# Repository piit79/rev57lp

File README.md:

# Rev57LP

(Formerly known by no-one as Reviung-ish56 LP :)

Low-profile 57-key ergonomic keyboard inspired by Reviung41. Uses hotswap sockets for Kailh Choc V1 (PG1350) switches.

Based on [reviung-ish](https://github.com/fredbabe/reviung_ish_pcb) by oddkeeb.

Main differences from Reviung41:

* Added number row
* Added two more bottom row keys
* Added one extra middle key
* Uses hotswap sockets for Kailh Choc V1 switches with Choc spacing (18x17 mm)

Further modifications made by 42. Keebs:

* 2x 1u space key instead of a 2u with a Choc stabiliser, because nobody likes stabs
* Slightly increased angle of the sides from 13° to 15°
* Added power switch and a battery footprint
* Mounting holes changed to through holes for 3 mm diameter brass standoffs
* Dropped the middle matrix column to free up one I/O pin
* Added stacked acrylic case consisting of switch, middle and bottom plates

Full kit available for purchase at [42. Keebs](https://42keebs.eu/shop/kits/pro-micro-based/rev57lp-50-low-profile-hotswap-ergo-kit/).

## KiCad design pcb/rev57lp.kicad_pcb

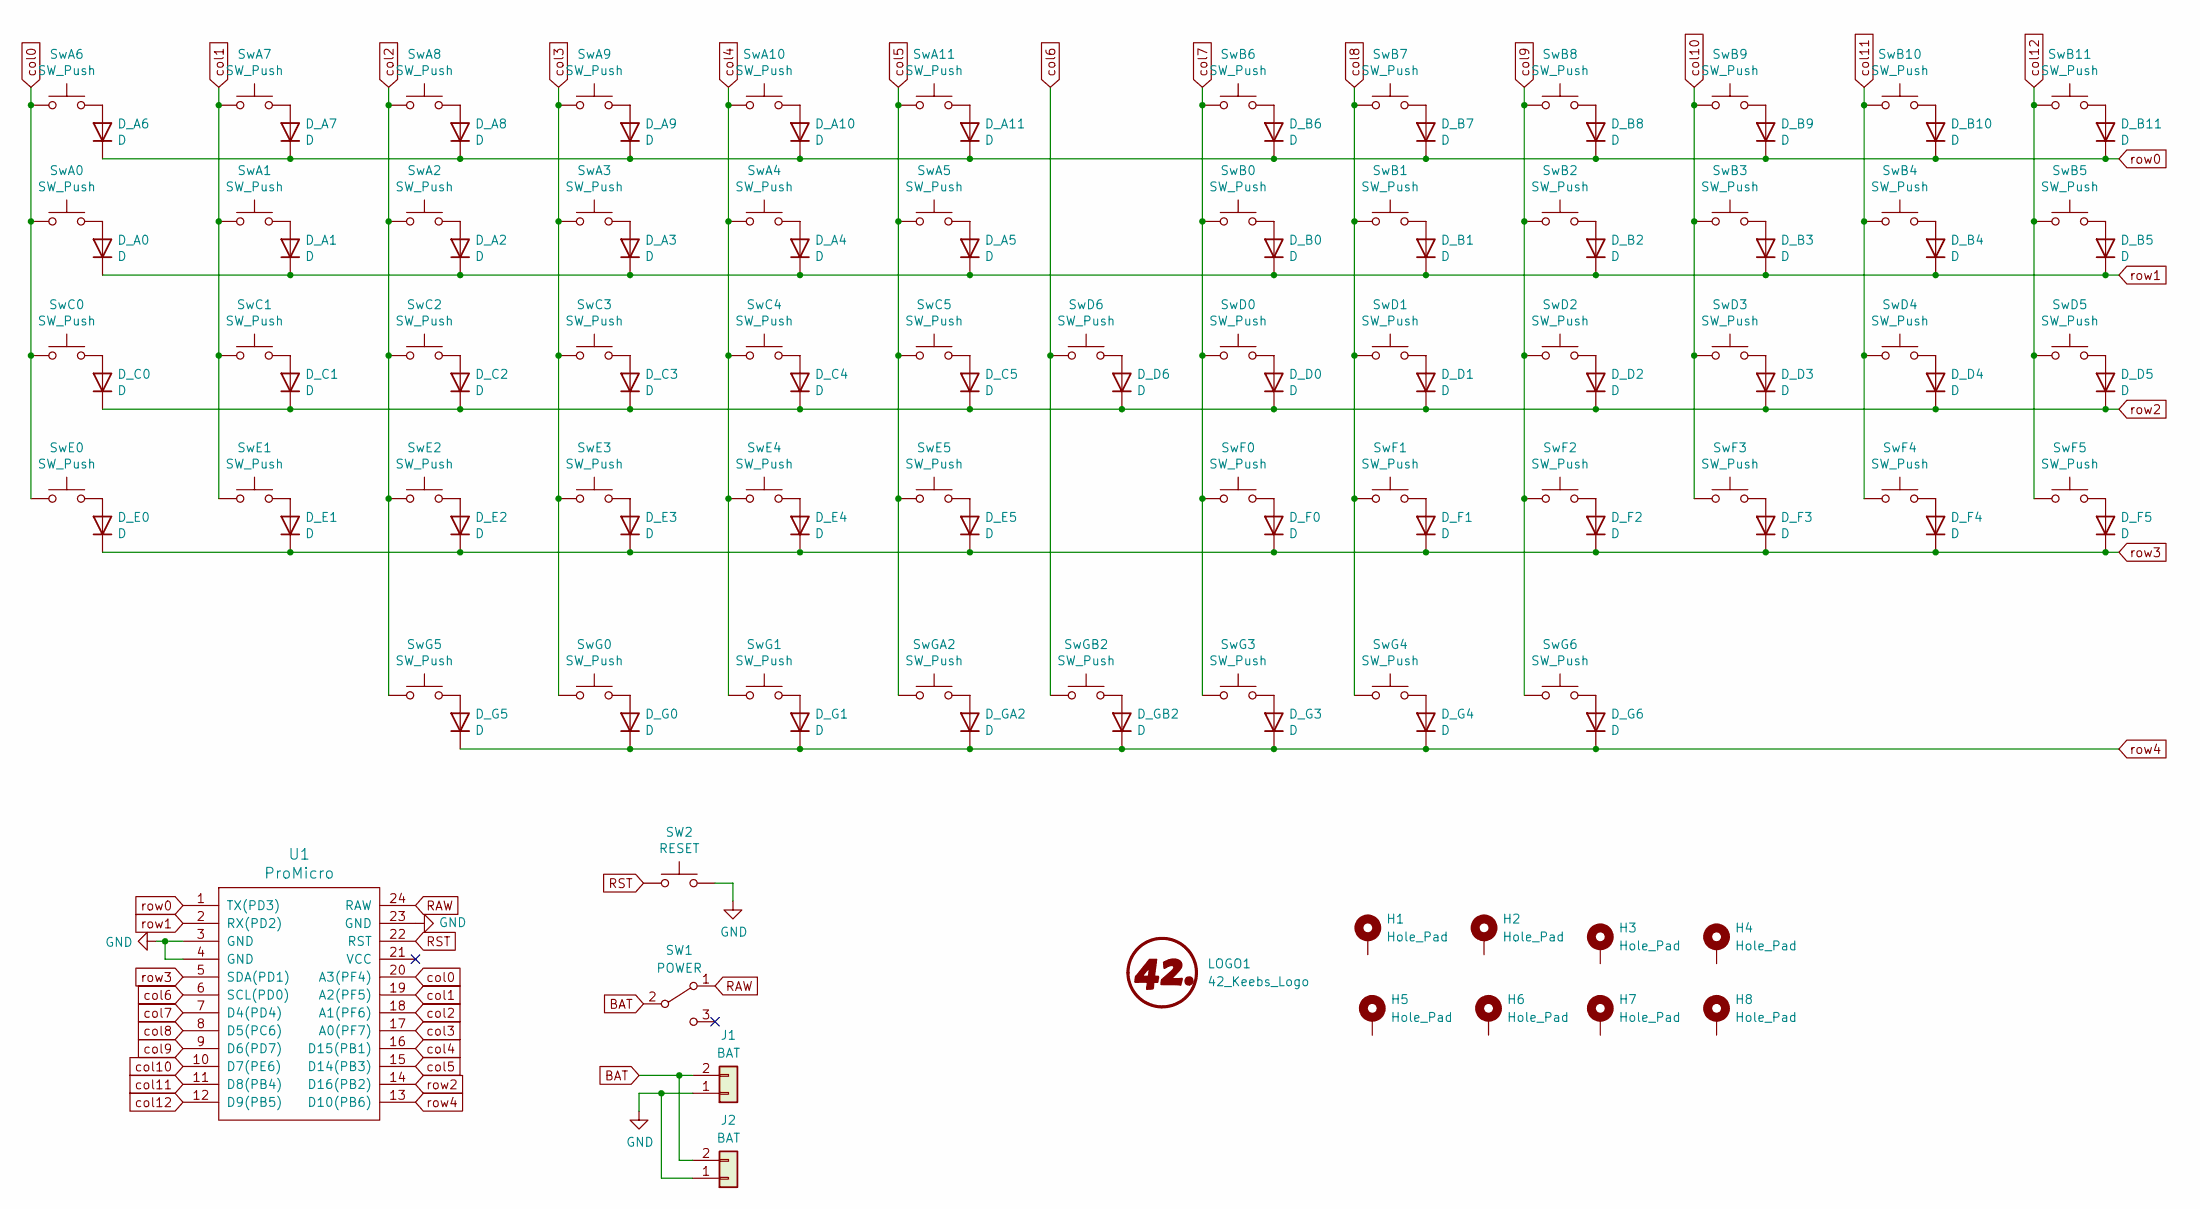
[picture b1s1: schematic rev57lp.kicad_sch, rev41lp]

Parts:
D_A0, D_A1, D_A2, D_A3, D_A4, D_A5, D_A6, D_A7, D_A8, D_A9, D_A10, D_A11: D; Diode_SOD123_dual_sided
D_B0, D_B1, D_B2, D_B3, D_B4, D_B5, D_B6, D_B7, D_B8, D_B9, D_B10, D_B11: D; Diode_SOD123_dual_sided
D_C0, D_C1, D_C2, D_C3, D_C4, D_C5: D; Diode_SOD123_dual_sided
D_D0, D_D1, D_D2, D_D3, D_D4, D_D5, D_D6: D; Diode_SOD123_dual_sided
D_E0, D_E1, D_E2, D_E3, D_E4, D_E5: D; Diode_SOD123_dual_sided
D_F0, D_F1, D_F2, D_F3, D_F4, D_F5: D; Diode_SOD123_dual_sided
D_G0, D_G1, D_G3, D_G4, D_G5, D_G6: D; Diode_SOD123_dual_sided
D_GA2: D; Diode_SOD123_dual_sided
D_GB2: D; Diode_SOD123_dual_sided
H1, H2, H3, H4, H5, H6, H7, H8: Hole_Pad; MountingHole_2.2mm_M2_Pad_Via
J1, J2: BAT; PinHeader_1x02_P2.54mm_Vertical
LOGO1: 42_Keebs_Logo; 42Keebs-icon-10mm-Mask
SW1: POWER; SW_CuK_JS202011AQN_DPDT_Angled
SW2: RESET; SW_SPST_TL3342
SwA0, SwA1, SwA2, SwA3, SwA4, SwA5, SwA6, SwA7, SwA8, SwA9, SwA10, SwA11: SW_Push; Kailh_socket_PG1350
SwB0, SwB1, SwB2, SwB3, SwB4, SwB5, SwB6, SwB7, SwB8, SwB9, SwB10, SwB11: SW_Push; Kailh_socket_PG1350
SwC0, SwC1, SwC2, SwC3, SwC4, SwC5: SW_Push; Kailh_socket_PG1350
SwD0, SwD1, SwD2, SwD3, SwD4, SwD5, SwD6: SW_Push; Kailh_socket_PG1350
SwE0, SwE1, SwE2, SwE3, SwE4, SwE5: SW_Push; Kailh_socket_PG1350
SwF0, SwF1, SwF2, SwF3, SwF4, SwF5: SW_Push; Kailh_socket_PG1350
SwG0, SwG1, SwG3, SwG4, SwG5, SwG6: SW_Push; Kailh_socket_PG1350
SwGA2: SW_Push; Kailh_socket_PG1350
SwGB2: SW_Push; Kailh_socket_PG1350
U1: ProMicro; ProMicro-USB-C

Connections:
GND: J1.1, J2.1, SW2.2, U1.3 (GND), U1.4 (GND), U1.23 (GND)
unnamed: D_A0.2 (A), SwA0.2
unnamed: D_A1.2 (A), SwA1.2
unnamed: D_A2.2 (A), SwA2.2
unnamed: D_A3.2 (A), SwA3.2
unnamed: D_A4.2 (A), SwA4.2
unnamed: D_A5.2 (A), SwA5.2
unnamed: D_A6.2 (A), SwA6.2
unnamed: D_A7.2 (A), SwA7.2
unnamed: D_A8.2 (A), SwA8.2
unnamed: D_A9.2 (A), SwA9.2
unnamed: D_A10.2 (A), SwA10.2
unnamed: D_A11.2 (A), SwA11.2
unnamed: D_B0.2 (A), SwB0.2
unnamed: D_B1.2 (A), SwB1.2
unnamed: D_B2.2 (A), SwB2.2
unnamed: D_B3.2 (A), SwB3.2
unnamed: D_B4.2 (A), SwB4.2
unnamed: D_B5.2 (A), SwB5.2
unnamed: D_B6.2 (A), SwB6.2
unnamed: D_B7.2 (A), SwB7.2
unnamed: D_B8.2 (A), SwB8.2
unnamed: D_B9.2 (A), SwB9.2
unnamed: D_B10.2 (A), SwB10.2
unnamed: D_B11.2 (A), SwB11.2
unnamed: D_C0.2 (A), SwC0.2
unnamed: D_C1.2 (A), SwC1.2
unnamed: D_C2.2 (A), SwC2.2
unnamed: D_C3.2 (A), SwC3.2
unnamed: D_C4.2 (A), SwC4.2
unnamed: D_C5.2 (A), SwC5.2
unnamed: D_D0.2 (A), SwD0.2
unnamed: D_D1.2 (A), SwD1.2
unnamed: D_D2.2 (A), SwD2.2
unnamed: D_D3.2 (A), SwD3.2
unnamed: D_D4.2 (A), SwD4.2
unnamed: D_D5.2 (A), SwD5.2
unnamed: D_D6.2 (A), SwD6.2
unnamed: D_E0.2 (A), SwE0.2
unnamed: D_E1.2 (A), SwE1.2
unnamed: D_E2.2 (A), SwE2.2
unnamed: D_E3.2 (A), SwE3.2
unnamed: D_E4.2 (A), SwE4.2
unnamed: D_E5.2 (A), SwE5.2
unnamed: D_F0.2 (A), SwF0.2
unnamed: D_F1.2 (A), SwF1.2
unnamed: D_F2.2 (A), SwF2.2
unnamed: D_F3.2 (A), SwF3.2
unnamed: D_F4.2 (A), SwF4.2
unnamed: D_F5.2 (A), SwF5.2
unnamed: D_G0.2 (A), SwG0.2
unnamed: D_G1.2 (A), SwG1.2
unnamed: D_G3.2 (A), SwG3.2
unnamed: D_G4.2 (A), SwG4.2
unnamed: D_G5.2 (A), SwG5.2
unnamed: D_G6.2 (A), SwG6.2
unnamed: D_GA2.2 (A), SwGA2.2
unnamed: D_GB2.2 (A), SwGB2.2
RST: SW2.1, U1.22 (RST)
col0: SwA0.1, SwA6.1, SwC0.1, SwE0.1, U1.20 (A3(PF4))
col1: SwA1.1, SwA7.1, SwC1.1, SwE1.1, U1.19 (A2(PF5))
col2: SwA2.1, SwA8.1, SwC2.1, SwE2.1, SwG5.1, U1.18 (A1(PF6))
col3: SwA3.1, SwA9.1, SwC3.1, SwE3.1, SwG0.1, U1.17 (A0(PF7))
col4: SwA4.1, SwA10.1, SwC4.1, SwE4.1, SwG1.1, U1.16 (D15(PB1))
col5: SwA5.1, SwA11.1, SwC5.1, SwE5.1, SwGA2.1, U1.15 (D14(PB3)); also elsewhere on the board
col6: SwD6.1, SwGB2.1, U1.6 (SCL(PD0)); also elsewhere on the board
col7: SwB0.1, SwB6.1, SwD0.1, SwF0.1, SwG3.1, U1.7 (D4(PD4))
col8: SwB1.1, SwB7.1, SwD1.1, SwF1.1, SwG4.1, U1.8 (D5(PC6))
col9: SwB2.1, SwB8.1, SwD2.1, SwF2.1, SwG6.1, U1.9 (D6(PD7))
col10: SwB3.1, SwB9.1, SwD3.1, SwF3.1, U1.10 (D7(PE6))
col11: SwB4.1, SwB10.1, SwD4.1, SwF4.1, U1.11 (D8(PB4))
col12: SwB5.1, SwB11.1, SwD5.1, SwF5.1, U1.12 (D9(PB5))
row0: D_A6.1 (K), D_A7.1 (K), D_A8.1 (K), D_A9.1 (K), D_A10.1 (K), D_A11.1 (K), D_B6.1 (K), D_B7.1 (K), D_B8.1 (K), D_B9.1 (K), D_B10.1 (K), D_B11.1 (K), U1.1 (TX(PD3))
row1: D_A0.1 (K), D_A1.1 (K), D_A2.1 (K), D_A3.1 (K), D_A4.1 (K), D_A5.1 (K), D_B0.1 (K), D_B1.1 (K), D_B2.1 (K), D_B3.1 (K), D_B4.1 (K), D_B5.1 (K), U1.2 (RX(PD2))
row2: D_C0.1 (K), D_C1.1 (K), D_C2.1 (K), D_C3.1 (K), D_C4.1 (K), D_C5.1 (K), D_D0.1 (K), D_D1.1 (K), D_D2.1 (K), D_D3.1 (K), D_D4.1 (K), D_D5.1 (K), D_D6.1 (K), U1.14 (D16(PB2))
row3: D_E0.1 (K), D_E1.1 (K), D_E2.1 (K), D_E3.1 (K), D_E4.1 (K), D_E5.1 (K), D_F0.1 (K), D_F1.1 (K), D_F2.1 (K), D_F3.1 (K), D_F4.1 (K), D_F5.1 (K), U1.5 (SDA(PD1))
row4: D_G0.1 (K), D_G1.1 (K), D_G3.1 (K), D_G4.1 (K), D_G5.1 (K), D_G6.1 (K), D_GA2.1 (K), D_GB2.1 (K), U1.13 (D10(PB6)); also elsewhere on the board

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
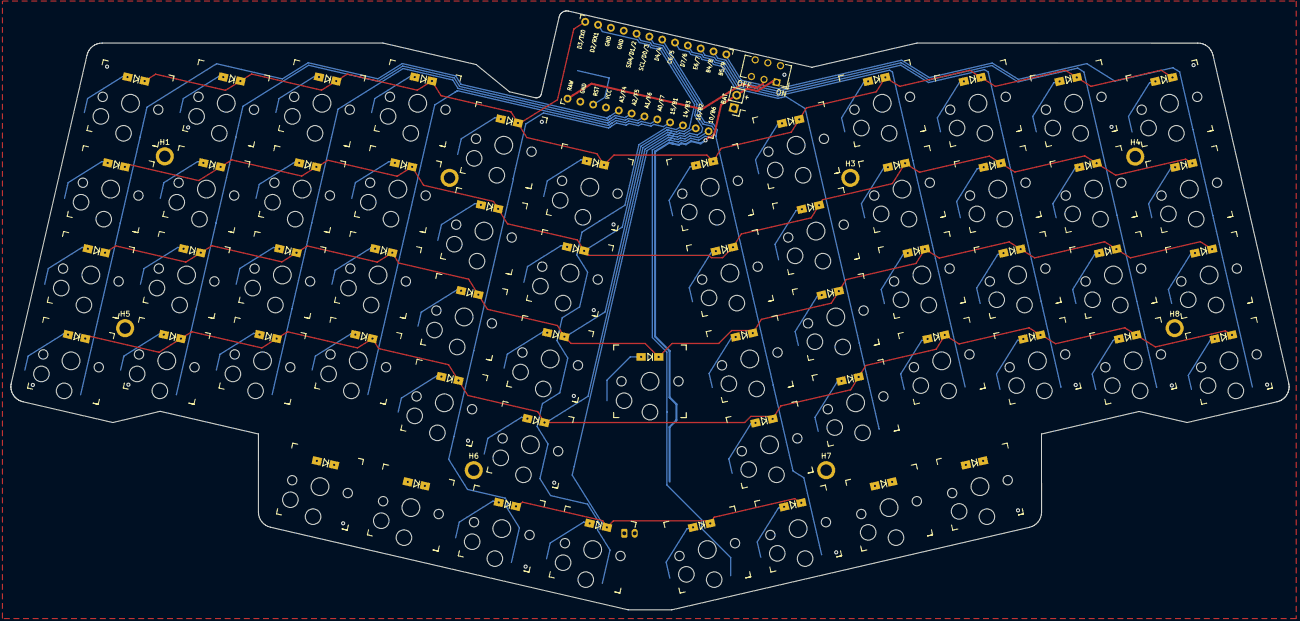
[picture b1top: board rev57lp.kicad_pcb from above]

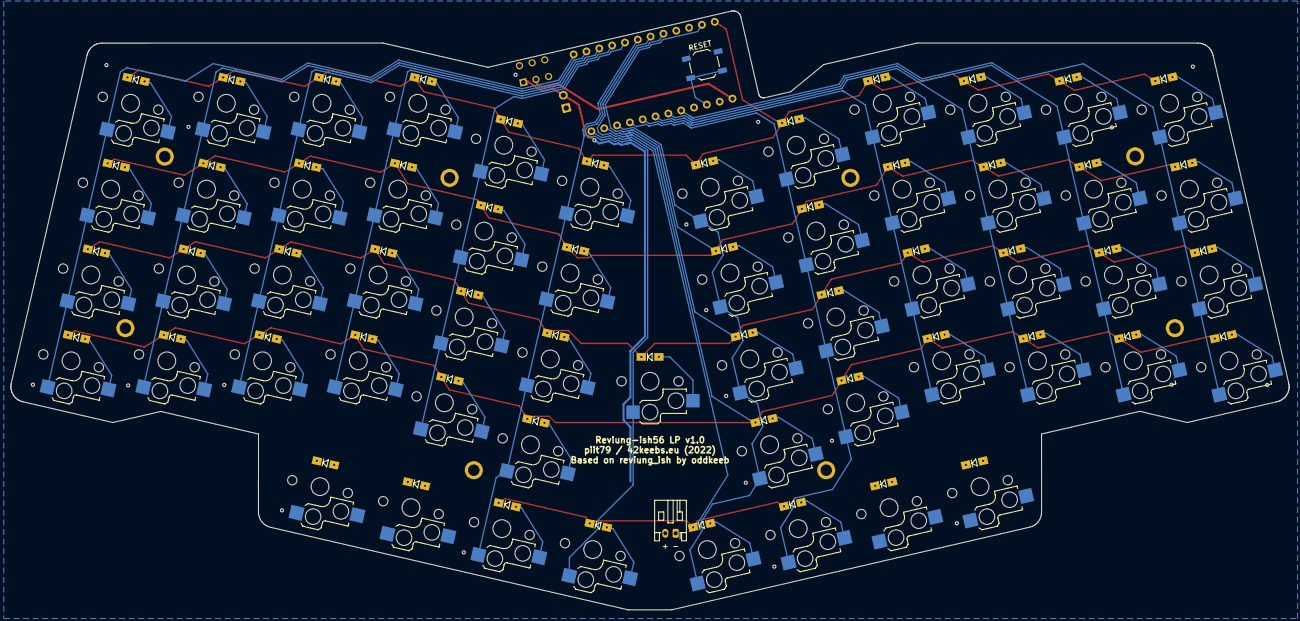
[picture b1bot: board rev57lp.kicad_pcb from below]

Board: 2 copper layers, 246.6 x 115.6 mm, 128 parts (59 on the bottom side), 79 nets.

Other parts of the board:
D_G2, D_G7: D; Diode_SOD123_dual_sided
SwG2, SwG7: SW_Push; Kailh_socket_PG1350_1u_sw_cap

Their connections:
unnamed: D_G2.2 (A), SwG2.2
unnamed: D_G7.2 (A), SwG7.2
col5: SwG7.1; also elsewhere on the board
col6: SwG2.1; also elsewhere on the board
row4: D_G2.1 (K), D_G7.1 (K); also elsewhere on the board

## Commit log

2022-06-15 Rename the project and the main folder
2022-06-15 Add .gitignore file
2022-06-16 Add 42. Keebs KiCad library as a submodule
2022-06-17 Move inner bottom mounting holes 1 row lower
2022-06-17 Update README and add PCB image
2022-06-17 Make outline more like Reviung41; chage bottom row mods to 1u; neater col/row routing
2022-06-17 Make diode footprints dual-sided
2022-06-20 Move one bottom-row switch one column left in preparation for 2x1u space
2022-06-21 Move Pro Micro footpring inwards and improve the outline around it
2022-06-21 Make diode footprints dual-sided again
2022-06-29 Update 42. Keebs library
2022-06-29 Add power switch and battery connectors; update Pro Micro and some switch footprints
2022-06-29 Use diode footprints from 42. Keebs lib; switch to standard hole footprints
2022-06-29 Add battery polarity labels; fix diode reference orientation
2022-06-29 Move bottom inner holes further towards the centre; fix top inner hole not symmetric
2022-06-29 Clean up unneeded graphics
2022-06-30 Improve some labels and a couple of traces
2022-06-30 Update README and the PCB render
2022-07-01 Improve row routing; fix missing 3D socket model on one footprint
2022-07-02 Remove the now unused General_footprints library and the other two nonexistent libraries
2022-07-02 Switch to standard mounting hole footprints; bump version to 0.95
2022-07-05 Update 42. Keebs library (new 3D models, updated footprints)
2023-02-22 Remove unneeded footprint library keeblib.pretty
2023-02-22 Rename project to Rev57LP
2023-02-22 Use 1.5u space; improve outline; add power switch and battery connectors; improve routing
2023-02-22 WIP: switch to 2x1u space; experiment with straight bottom row
2023-02-22 Increase the angle of the sides to 15 degrees; update README
2023-03-08 Update the 42. Keebs KiCad library
2023-03-08 Bunch of modifications and tweaks:
    * Drop the middle matrix column to free up one I/O pin
    * Use dual DPDT switch symbol to fix DRC warnings about pins with no net
    * Use standoff through holes instead of M2 mounting holes
2023-07-18 Use switch footprints with mid plte cutouts; add other mid plate cutouts
2023-07-18 Add acrylic switch, mid and bottom plate files
